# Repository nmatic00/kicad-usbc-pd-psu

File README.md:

# USB-C PD Adjustable Power Supply

Based on [FEDEVEL](https://github.com/FEDEVEL/usbc-advanced-power-supply) design.
A compact USB-C Power Delivery (PD) power supply that accepts power from a USB-C PD adapter and provides a manually selectable output voltage through a DIP switch.

## Features

- USB-C PD input
- Up to **100 W** PD capability
- **5 V, 9 V, 12 V, 15 V, and 20 V** selectable outputs
- Manual voltage selection using a DIP switch
- **CH224K** USB-C PD sink controller
- LED indication of the selected output voltage
- Error indication for unsuccessful PD negotiation
- 3.3 V auxiliary supply using a **TPS70933DBVR** LDO
- 4-layer PCB with dedicated ground and power planes
- 90 Ω controlled-impedance USB 2.0 differential pair

## License
[CreativeCommons-Attribution-NonCommercial-ShareAlike 4.0 International](https://creativecommons.org/licenses/by-nc-sa/4.0/?ref=chooser-v1)

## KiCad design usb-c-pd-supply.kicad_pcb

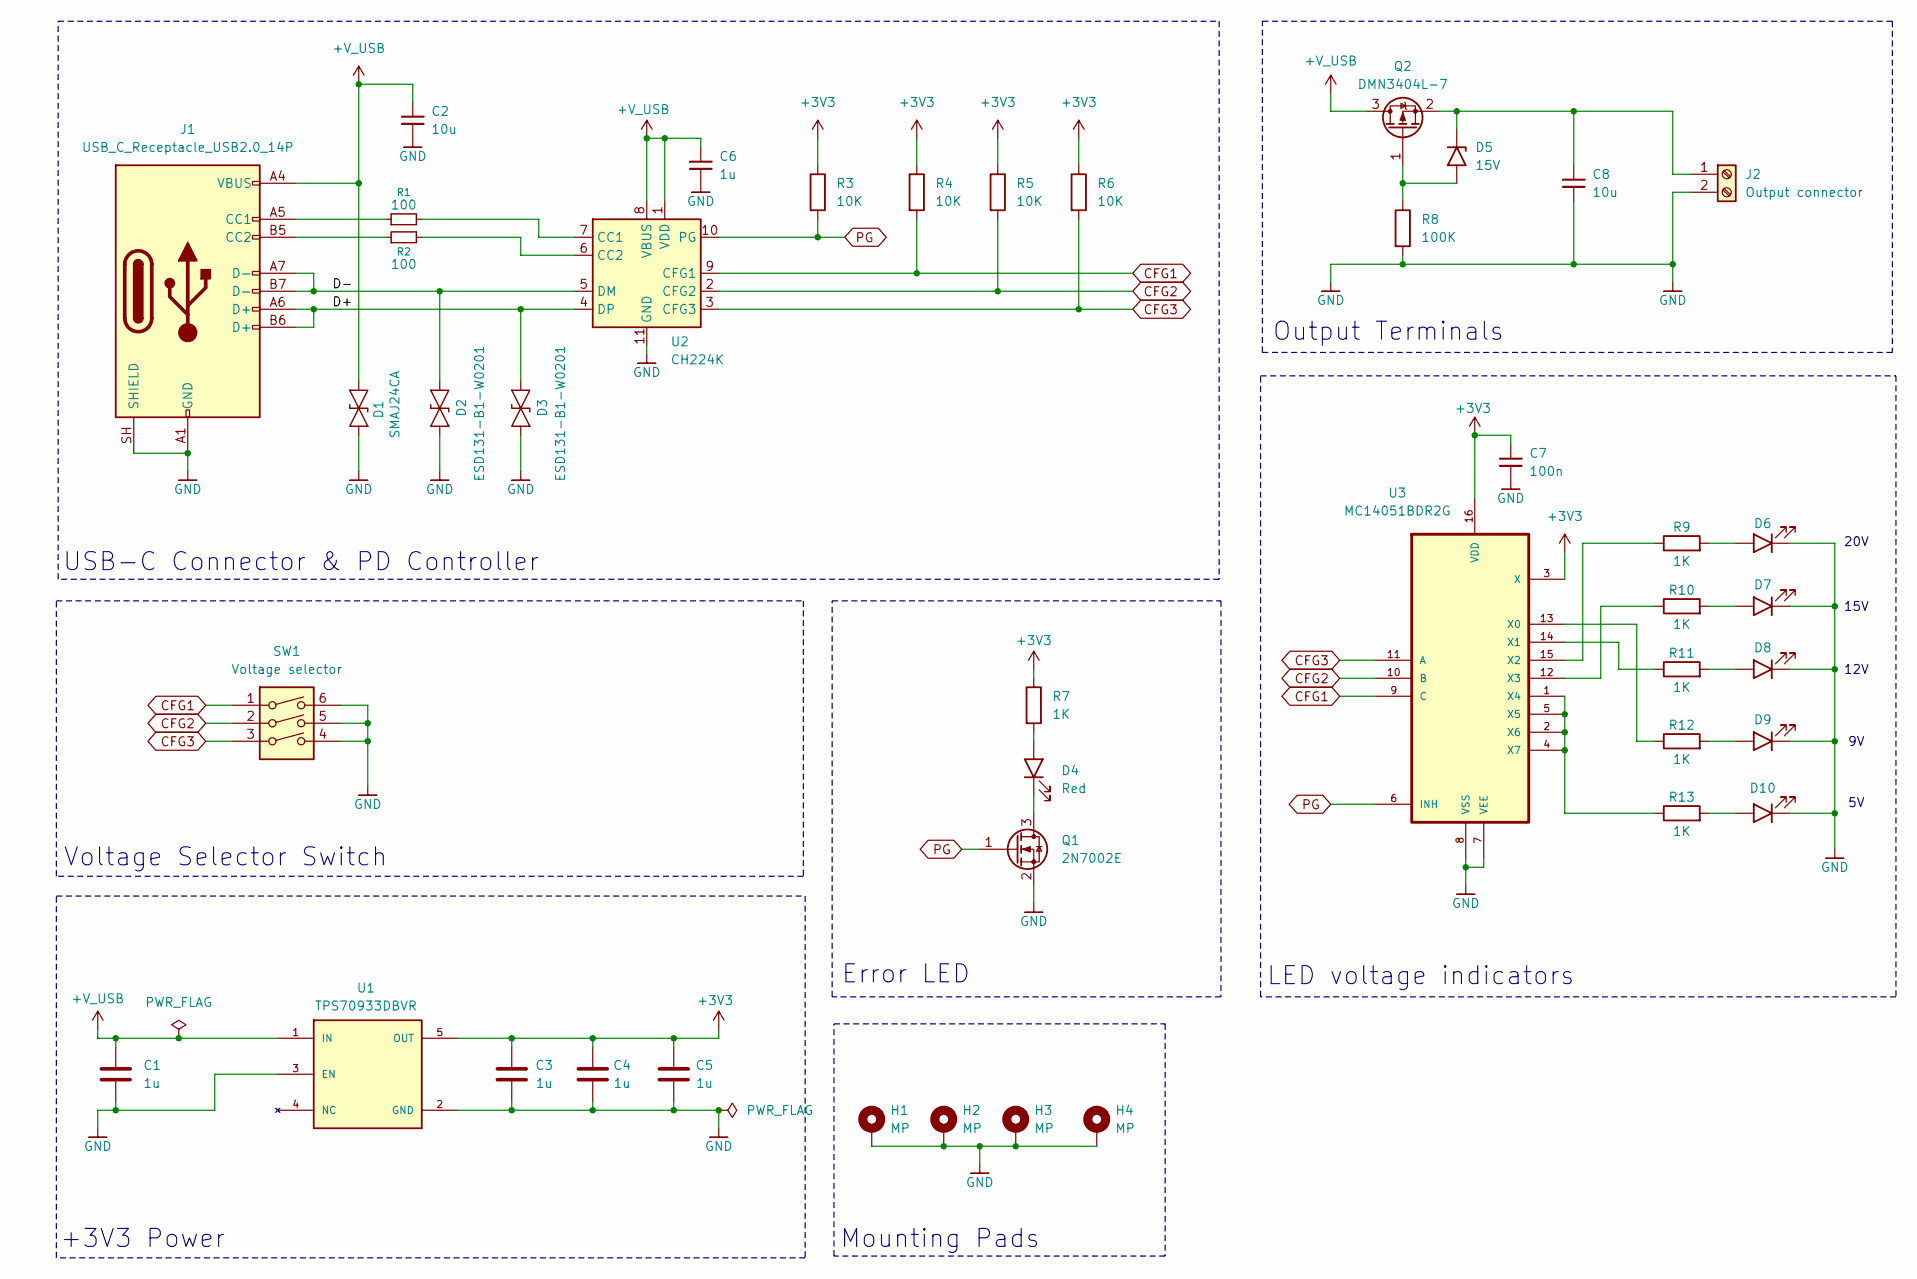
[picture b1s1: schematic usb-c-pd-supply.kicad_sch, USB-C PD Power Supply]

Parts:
C1, C3, C4, C5, C6: 1u; C_0603_1608Metric
C2, C8: 10u; R_1210_3225Metric
C7: 100n; C_0603_1608Metric
D1: SMAJ24CA; D_SMA
D2, D3: ESD131-B1-W0201; Infineon_SG-WLL-2-3_0.58x0.28_P0.36mm
D4: Red; LED_0805_2012Metric
D5: 15V; D_SOD-323
D6, D7, D8, D9, D10: Green; LED_0805_2012Metric
H1, H2, H3, H4: MP; MountingHole_2.2mm_M2_DIN965_Pad_TopBottom
J1: USB_C_Receptacle_USB2.0_14P; USB_C_Receptacle_GCT_USB4105-xx-A_16P_TopMnt_Horizontal
J2: Output connector; TerminalBlock_Phoenix_MKDS-1-2-3.81_1x02_P3.81mm_Horizontal
Q1: 2N7002E; SOT-23
Q2: DMN3404L-7; SOT-23
R1, R2: 100; R_0805_2012Metric
R3, R4, R5, R6: 10K; R_0805_2012Metric
R7, R9, R10, R11, R12, R13: 1K; R_0805_2012Metric
R8: 100K; R_0805_2012Metric
SW1: Voltage selector; SW_DIP_SPSTx03_Slide_6.7x9.18mm_W8.61mm_P2.54mm_LowProfile
U1: TPS70933DBVR; SOT95P280X145-5N; PARTREV H
U2: CH224K; SSOP-10-1EP_3.9x4.9mm_P1mm_EP2.1x3.3mm
U3: MC14051BDR2G; SOIC127P600X175-16N

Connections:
+3V3: C3.1, C4.1, C5.1, C7.1, R3.1, R4.1, R5.1, R6.1, R7.1, U1.5 (OUT), U3.3 (X), U3.16 (VDD)
+V_USB: C1.1, C2.1, C6.1, D1.2 (A2), J1.A4 (VBUS), J1.A9 (VBUS), J1.B4 (VBUS), J1.B9 (VBUS), Q2.3 (D), U1.1 (IN), U2.1 (VDD), U2.8 (VBUS)
/D+: D3.2 (A2), J1.A6 (D+), J1.B6 (D+), U2.4 (DP)
/D-: D2.2 (A2), J1.A7 (D-), J1.B7 (D-), U2.5 (DM)
CFG1: R4.2, SW1.1, U2.9 (CFG1), U3.9 (C)
CFG2: R5.2, SW1.2, U2.2 (CFG2), U3.10 (B)
CFG3: R6.2, SW1.3, U2.3 (CFG3), U3.11 (A)
GND: C1.2, C2.2, C3.2, C4.2, C5.2, C6.2, C7.2, C8.2, D1.1 (A1), D2.1 (A1), D3.1 (A1), D6.1 (K), D7.1 (K), D8.1 (K), D9.1 (K), D10.1 (K), H1.1 (1_1), H2.1 (1_1), H3.1 (1_1), H4.1 (1_1), J1.A1 (GND), J1.A12 (GND), J1.B1 (GND), J1.B12 (GND), J1.SH (SHIELD), J2.2, Q1.2 (S), R8.2, SW1.4, SW1.5, SW1.6, U1.2 (GND), U1.3 (EN), U2.11 (GND), U3.7 (VEE), U3.8 (VSS)
unnamed: D4.2 (A), R7.2
unnamed: D4.1 (K), Q1.3 (D)
unnamed: D5.2 (A), Q2.1 (G), R8.1
unnamed: C8.1, D5.1 (K), J2.1, Q2.2 (S)
unnamed: D6.2 (A), R9.2
unnamed: D7.2 (A), R10.2
unnamed: D8.2 (A), R11.2
unnamed: D9.2 (A), R12.2
unnamed: D10.2 (A), R13.2
unnamed: J1.A5 (CC1), R1.1
unnamed: J1.B5 (CC2), R2.1
unnamed: R1.2, U2.7 (CC1)
unnamed: R2.2, U2.6 (CC2)
unnamed: R12.1, U3.13 (X0)
unnamed: R11.1, U3.14 (X1)
unnamed: R9.1, U3.15 (X2)
unnamed: R10.1, U3.12 (X3)
unnamed: R13.1, U3.1 (X4), U3.2 (X6), U3.4 (X7), U3.5 (X5)
PG: Q1.1 (G), R3.2, U2.10 (PG), U3.6 (INH)

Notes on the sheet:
Mounting Pads
12V
20V
USB-C Connector & PD Controller
+3V3 Power
Voltage Selector Switch
Error LED
LED voltage indicators
Output Terminals
15V

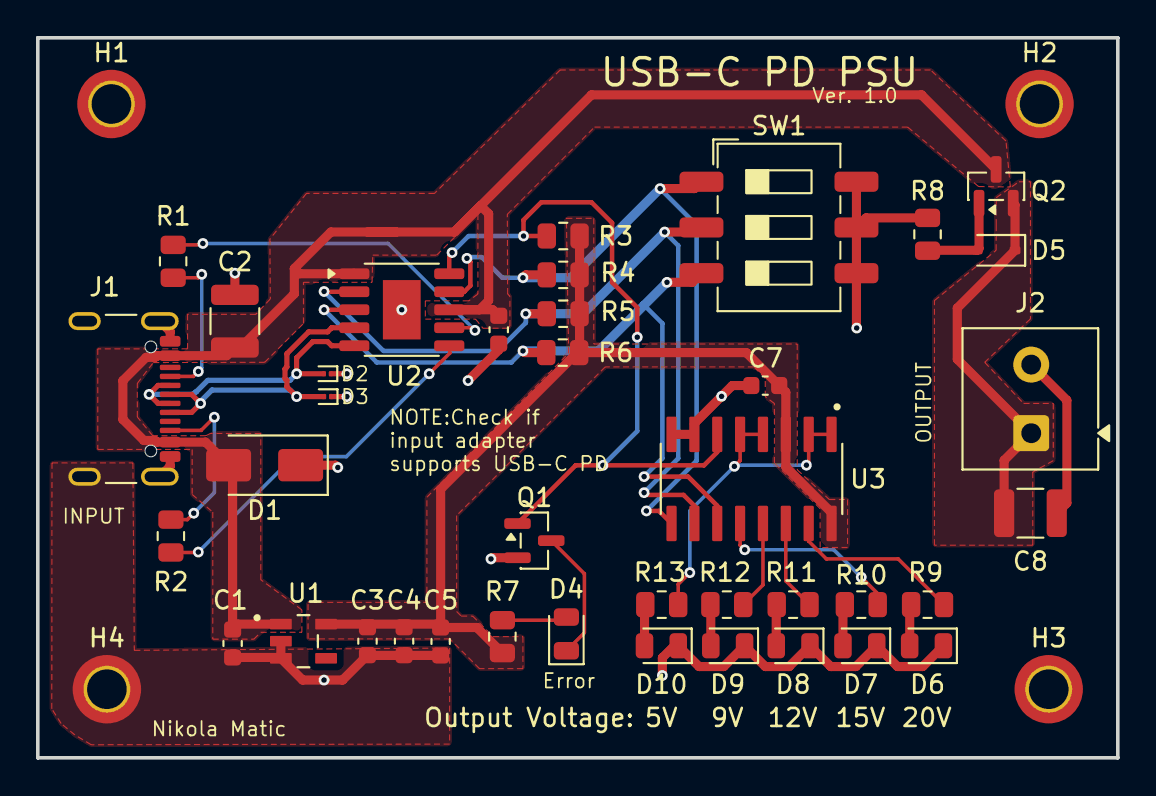
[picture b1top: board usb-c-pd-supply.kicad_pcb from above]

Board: 4 copper layers, 60.0 x 40.0 mm, 43 parts (0 on the bottom side), 27 nets.
